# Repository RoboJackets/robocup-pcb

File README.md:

RoboCup PCB Repository
===========
Welcome to the Georgia Tech RoboJackets repository for management and storage of RoboCup's hardware files! Additional information about the team and current projects can be found on the [RoboJackets Website](http://www.robojackets.org/teams/robocup/) and the [RoboJacket Wiki](http://wiki.robojackets.org/w/RoboCup).

If you are a new member to the RoboCup electrical team and have never used *[git version control](http://git-scm.com/)* before, we highly recommend that you familiarize yourself with it by reading [this guide](https://git-scm.com/book/en/v2).

## Prerequisites
- A computer configured with git [[Linux (Preferred)](https://git-scm.com/install/linux)] [[Windows](https://windows.github.com)] [[Mac](https://mac.github.com/)]
- An installation of [KiCAD v10.0](http://kicad-pcb.org/download/)
- An installation of [Obsidian](https://obsidian.md/download)

## Setup

### Cloning the Repository
To clone the repository, run the following command in your terminal:
```
git clone git@github.com:RoboJackets/robocup-pcb.git
```

## Board Archives
All currently deployed boards as of 2026 were designed using KiCAD.

However, older boards in the archives were designed using [EAGLE](http://www.cadsoftusa.com/) or [PCB](http://pcb.geda-project.org) (a program that is part of the [gEDA project](http://www.geda-project.org))

Unfortunately, EAGLE and PCB are no longer supported by their respective companies, and are not available for download. If you need access to these files, you are on your own.

## License

This project is licensed under the Apache License v2.0.  See the [LICENSE](LICENSE) file for more information.

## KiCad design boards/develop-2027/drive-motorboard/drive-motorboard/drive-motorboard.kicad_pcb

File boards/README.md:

# Style Guide

## Schematic Style
* Always snap to 0.1 inch grid
* Insert appropriate size frame for each sheet
    * Set Global Attributes for `REVISION` and `TEAM`
    * Set Attribute of frame for `SCH_DESC`

## Board Style
* Attempt to keep snapped to 0.5 mm (with 0.25 alt) with 90º or 45º angles

## Library Style
#### Symbol
* Always keep pins aligned to 0.1 inch grid
* Add Name and Value on correct layers

#### Package
* Add Name and Value on correct layers
* Silkscreen on `TPLACE` should not go over pad
* Use `TDOCU` to show accurate package outline

#### Device
* Final Device ideally be actual part number unless generic part where many possibles could be used
* Use wildcard when using multiple packages with one symbol
* Add correct prefix for component type ([reference](https://en.wikipedia.org/wiki/Reference_designator)), common components:
    * C : Capacitor
    * L : Inductor
    * R : Resistor
    * D : Diodes (including LEDs)
    * J : Jack (least movable part of connector)
    * Q : Transistor
    * F : Fuse
* Add manufacturer part number and (when possible) Digikey part number as attributes `MPN` and `DIGIKEY` respectivly
    * Do this for each technology and variant combination

# Finalize Board

When board completely done and ready to order ensure the following are completed:
* Board folder named "board-name"-v"version"
* Export board to PNG and place in folder
* Create README.md with description of the board and PNG of the board
* Create gerber.zip file of all Gerber files to be sent to board fab
* After all items added for board, make final commit for board version and tag commit as "board-name"-v"version"
* Once pushed to Github create release of board from tag consisting of list of changes from past version, link to gerber.zip (Github raw link for that tag), and PNG of board
    * For prototypes mark release as pre-release

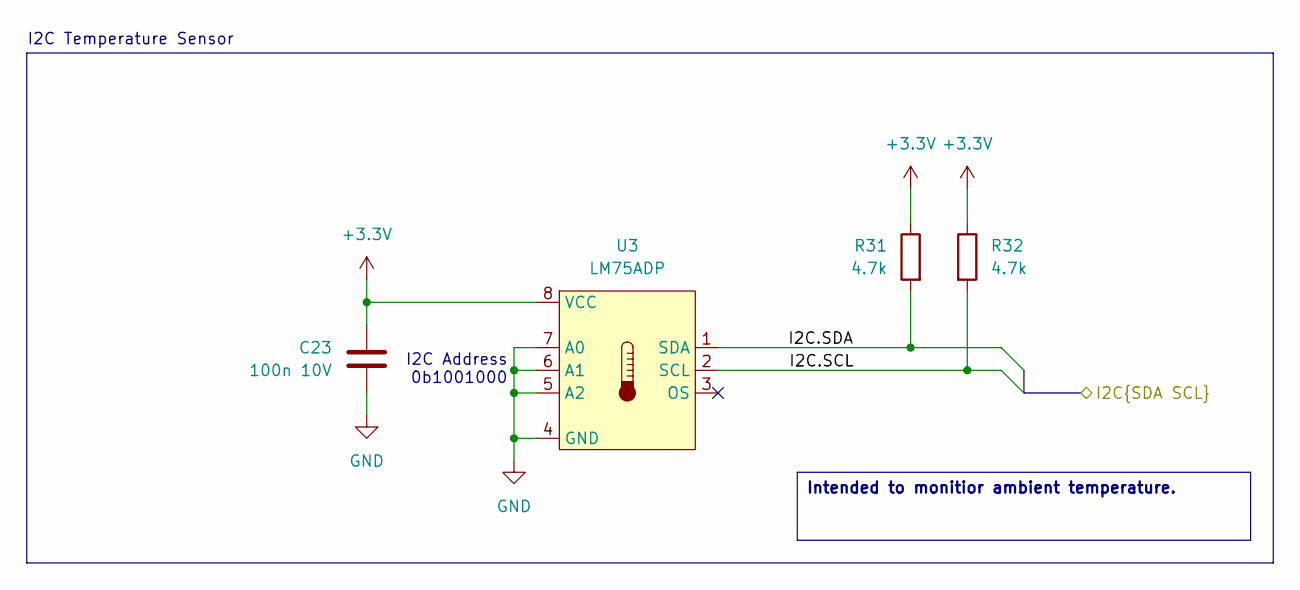
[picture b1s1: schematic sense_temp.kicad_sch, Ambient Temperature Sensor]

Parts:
C23: 100n 10V; C_0402_1005Metric; Manufacturer P/N CL05A104KA5NNNC
R31, R32: 4.7k; R_0402_1005Metric; Manufacturer P/N RC0402FR-074K7L
U3: LM75ADP; TSSOP-8_3x3mm_P0.65mm; Manufacturer P/N LM75ADP,118

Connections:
+3.3V: C23.1, R31.1, R32.1, U3.8 (VCC); also elsewhere on the board
/Motor Controller/I2C.SCL: R32.2, U3.2 (SCL); also elsewhere on the board
/Motor Controller/I2C.SDA: R31.2, U3.1 (SDA); also elsewhere on the board
GND: C23.2, U3.4 (GND), U3.5 (A2), U3.6 (A1), U3.7 (A0); also elsewhere on the board

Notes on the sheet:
I2C Address 0b1001000
I2C Temperature Sensor
Intended to monitior ambient temperature.

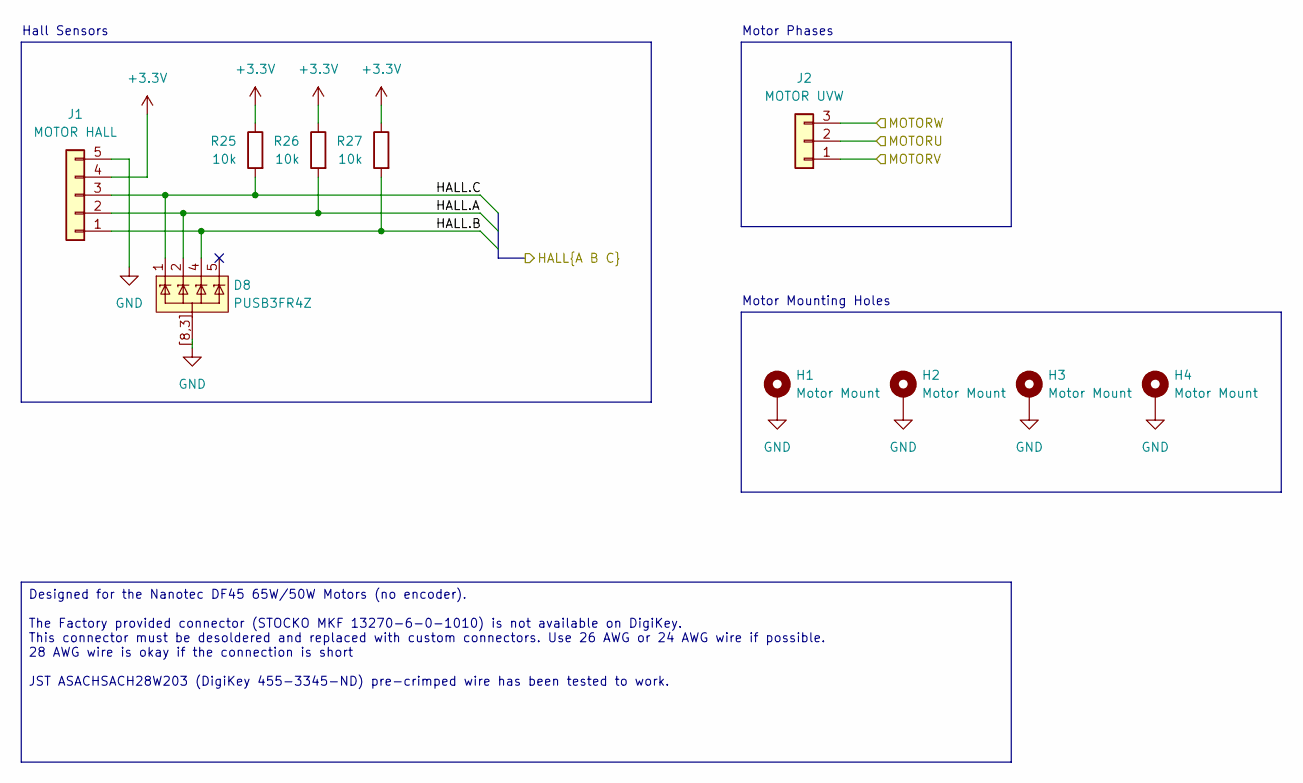
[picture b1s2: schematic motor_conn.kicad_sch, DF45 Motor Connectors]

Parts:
D8: PUSB3FR4Z; Diodes_UDFN-10_1x2.5mm_P0.5mm; Manufacturer P/N PUSB3FR4Z
H1: Motor Mount; MountingHole_3.2mm_M3_Pad; Manufacturer P/N H1
H2: Motor Mount; MountingHole_3.2mm_M3_Pad; Manufacturer P/N H2
H3: Motor Mount; MountingHole_3.2mm_M3_Pad; Manufacturer P/N H3
H4: Motor Mount; MountingHole_3.2mm_M3_Pad; Manufacturer P/N H4
J1: MOTOR HALL; JST_ACH_BM05B-ACHSS-A-GAN-ETF_1x05-1MP_P1.20mm_Vertical; Manufacturer P/N BM05B-ACHSS-A-GAN-ETF
J2: MOTOR UVW; JST_ACH_BM03B-ACHSS-GAN-ETF_1x03-1MP_P1.20mm_Vertical; Manufacturer P/N BM03B-ACHSS-GAN-TF
R25, R26, R27: 10k; R_0402_1005Metric; Manufacturer P/N RC0402FR-0710KL

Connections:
+3.3V: J1.4, R25.1, R26.1, R27.1; also elsewhere on the board
/Motor Connections/HALL.A: D8.2 (CH2), J1.2, R26.2; also elsewhere on the board
/Motor Connections/HALL.B: D8.4 (CH3), J1.1, R27.2; also elsewhere on the board
/Motor Connections/HALL.C: D8.1 (CH1), J1.3, R25.2; also elsewhere on the board
/Motor Connections/MOTORU: J2.2; also elsewhere on the board
/Motor Connections/MOTORV: J2.1; also elsewhere on the board
/Motor Connections/MOTORW: J2.3; also elsewhere on the board
GND: D8.3 (GND), D8.8 (GND), D8.[8,3] (GND), H1.1 (1_1), H2.1 (1_1), H3.1 (1_1), H4.1 (1_1), J1.5; also elsewhere on the board

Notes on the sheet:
Hall Sensors
Motor Phases
Motor Mounting Holes
Designed for the Nanotec DF45 65W/50W Motors (no encoder). The Factory provided connector (STOCKO MKF 13270-6-0-1010) is not available on DigiKey. This connector must be desoldered and replaced with custom connectors. Use 26 AWG or 24 AWG wire if possible. 28 AWG wire is okay if the connection is s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

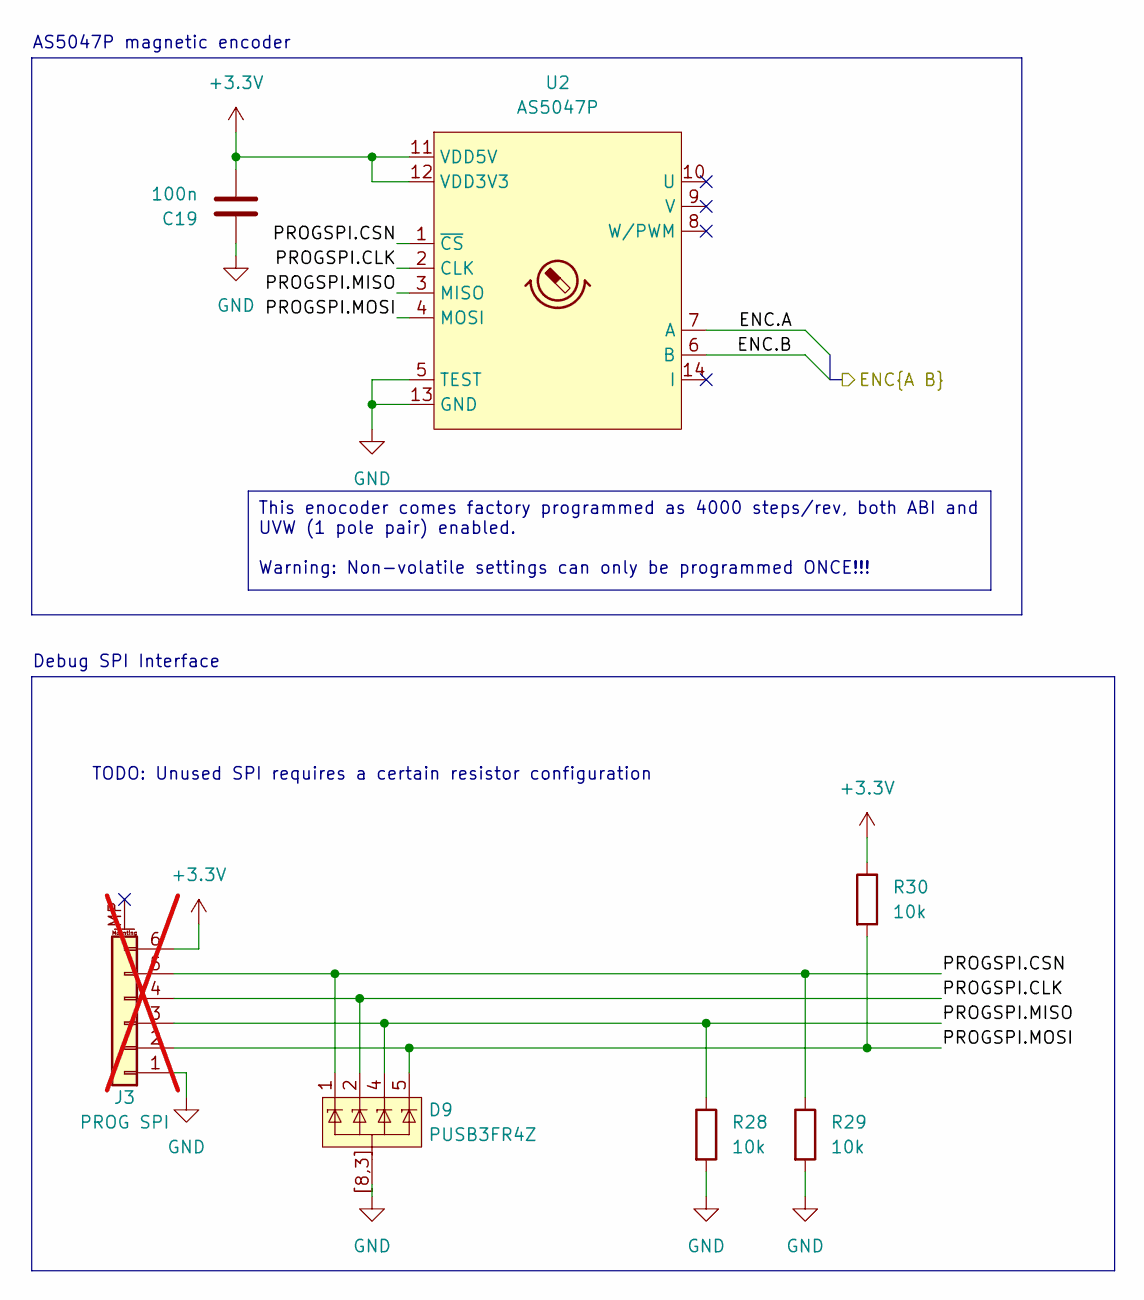
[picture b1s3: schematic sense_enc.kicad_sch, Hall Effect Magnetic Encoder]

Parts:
C19: 100n; C_0402_1005Metric; Manufacturer P/N CL05A104KA5NNNC
D9: PUSB3FR4Z; Diodes_UDFN-10_1x2.5mm_P0.5mm; Manufacturer P/N PUSB3FR4Z
J3: PROG SPI; JST_GH_SM06B-GHS-TB_1x06-1MP_P1.25mm_Horizontal; Manufacturer P/N SM06B-GHS-TB; not fitted
R28, R29, R30: 10k; R_0402_1005Metric; Manufacturer P/N RC0402FR-0710KL
U2: AS5047P; TSSOP-14_4.4x5mm_P0.65mm; Manufacturer P/N AS5047P

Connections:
+3.3V: C19.2, J3.6, R30.1, U2.11 (VDD5V), U2.12 (VDD3V3); also elsewhere on the board
/Magnetic Encoder/ENC.A: U2.7 (A); also elsewhere on the board
/Magnetic Encoder/ENC.B: U2.6 (B); also elsewhere on the board
/Magnetic Encoder/PROGSPI.CLK: D9.2 (CH2), J3.4, U2.2 (CLK)
/Magnetic Encoder/PROGSPI.CSN: D9.1 (CH1), J3.5, R29.1, U2.1 (~CS)
/Magnetic Encoder/PROGSPI.MISO: D9.4 (CH3), J3.3, R28.1, U2.3 (MISO)
/Magnetic Encoder/PROGSPI.MOSI: D9.5 (CH4), J3.2, R30.2, U2.4 (MOSI)
GND: C19.1, D9.3 (GND), D9.8 (GND), D9.[8,3] (GND), J3.1, R28.2, R29.2, U2.5 (TEST), U2.13 (GND); also elsewhere on the board

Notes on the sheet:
TODO: Unused SPI requires a certain resistor configuration
Debug SPI Interface
AS5047P magnetic encoder
This enocoder comes factory programmed as 4000 steps/rev, both ABI and UVW (1 pole pair) enabled. Warning: Non-volatile settings can only be programmed ONCE!!!

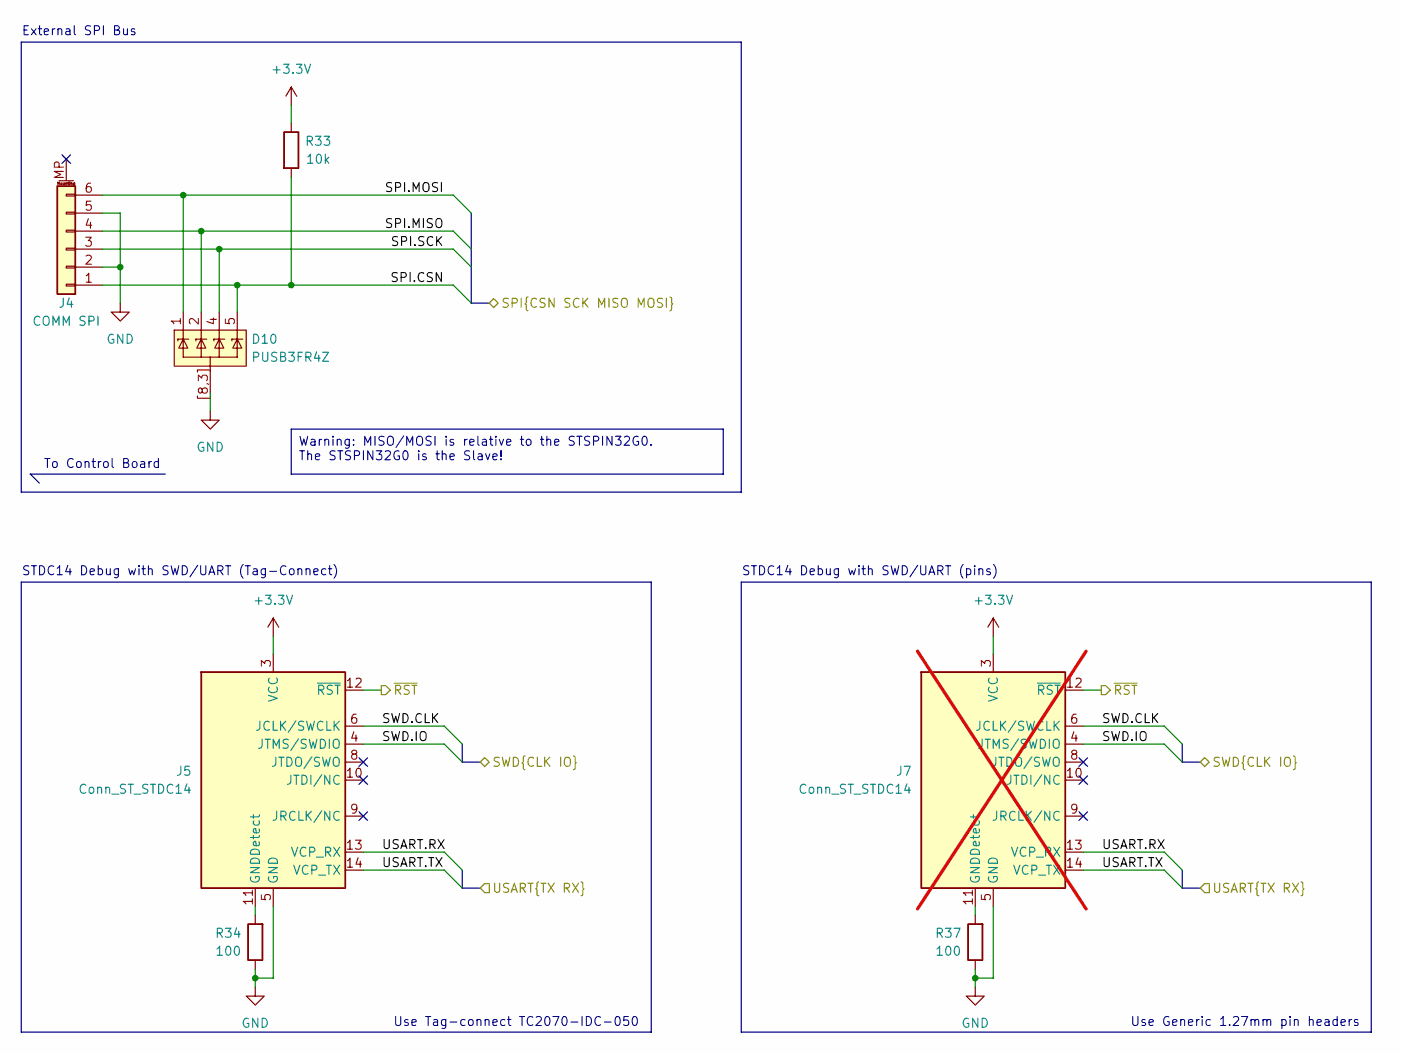
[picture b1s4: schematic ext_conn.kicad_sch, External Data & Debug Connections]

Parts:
D10: PUSB3FR4Z; Diodes_UDFN-10_1x2.5mm_P0.5mm; Manufacturer P/N PUSB3FR4Z
J4: COMM SPI; JST_GH_SM06B-GHS-TB_1x06-1MP_P1.25mm_Horizontal; Manufacturer P/N SM06B-GHS-TB
J5: Conn_ST_STDC14; Tag-Connect_TC2070-IDC-FP_2x07_P1.27mm_Vertical; Manufacturer P/N J5
J7: Conn_ST_STDC14; PinHeader_2x07_P1.27mm_Vertical_SMD; Manufacturer P/N FTSH-107-01-L-DV-K; not fitted
R33: 10k; R_0402_1005Metric; Manufacturer P/N RC0402FR-0710KL
R34, R37: 100; R_0402_1005Metric; Manufacturer P/N RC0402FR-07100RL

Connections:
+3.3V: J5.3 (VCC), J7.3 (VCC), R33.1; also elsewhere on the board
/External Connections/SPI.CSN: D10.5 (CH4), J4.1, R33.2; also elsewhere on the board
/External Connections/SPI.MISO: D10.2 (CH2), J4.4; also elsewhere on the board
/External Connections/SPI.MOSI: D10.1 (CH1), J4.6; also elsewhere on the board
/External Connections/SPI.SCK: D10.4 (CH3), J4.3; also elsewhere on the board
/External Connections/SWD.CLK: J5.6 (JCLK/SWCLK), J7.6 (JCLK/SWCLK); also elsewhere on the board
/External Connections/SWD.IO: J5.4 (JTMS/SWDIO), J7.4 (JTMS/SWDIO); also elsewhere on the board
/External Connections/USART.RX: J5.13 (VCP_RX), J7.13 (VCP_RX); also elsewhere on the board
/External Connections/USART.TX: J5.14 (VCP_TX), J7.14 (VCP_TX); also elsewhere on the board
/External Connections/~RST: J5.12 (~RST), J7.12 (~RST); also elsewhere on the board
GND: D10.3 (GND), D10.8 (GND), D10.[8,3] (GND), J4.2, J4.5, J5.5 (GND), J5.7 (GND), J7.5 (GND), J7.7 (GND), R34.1, R37.1; also elsewhere on the board
unnamed: J5.11 (GNDDetect), R34.2
unnamed: J7.11 (GNDDetect), R37.2

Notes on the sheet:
External SPI Bus
To Control Board
STDC14 Debug with SWD/UART (pins)
STDC14 Debug with SWD/UART (Tag-Connect)
Use Generic 1.27mm pin headers
Use Tag-connect TC2070-IDC-050
Warning: MISO/MOSI is relative to the STSPIN32G0. The STSPIN32G0 is the Slave!

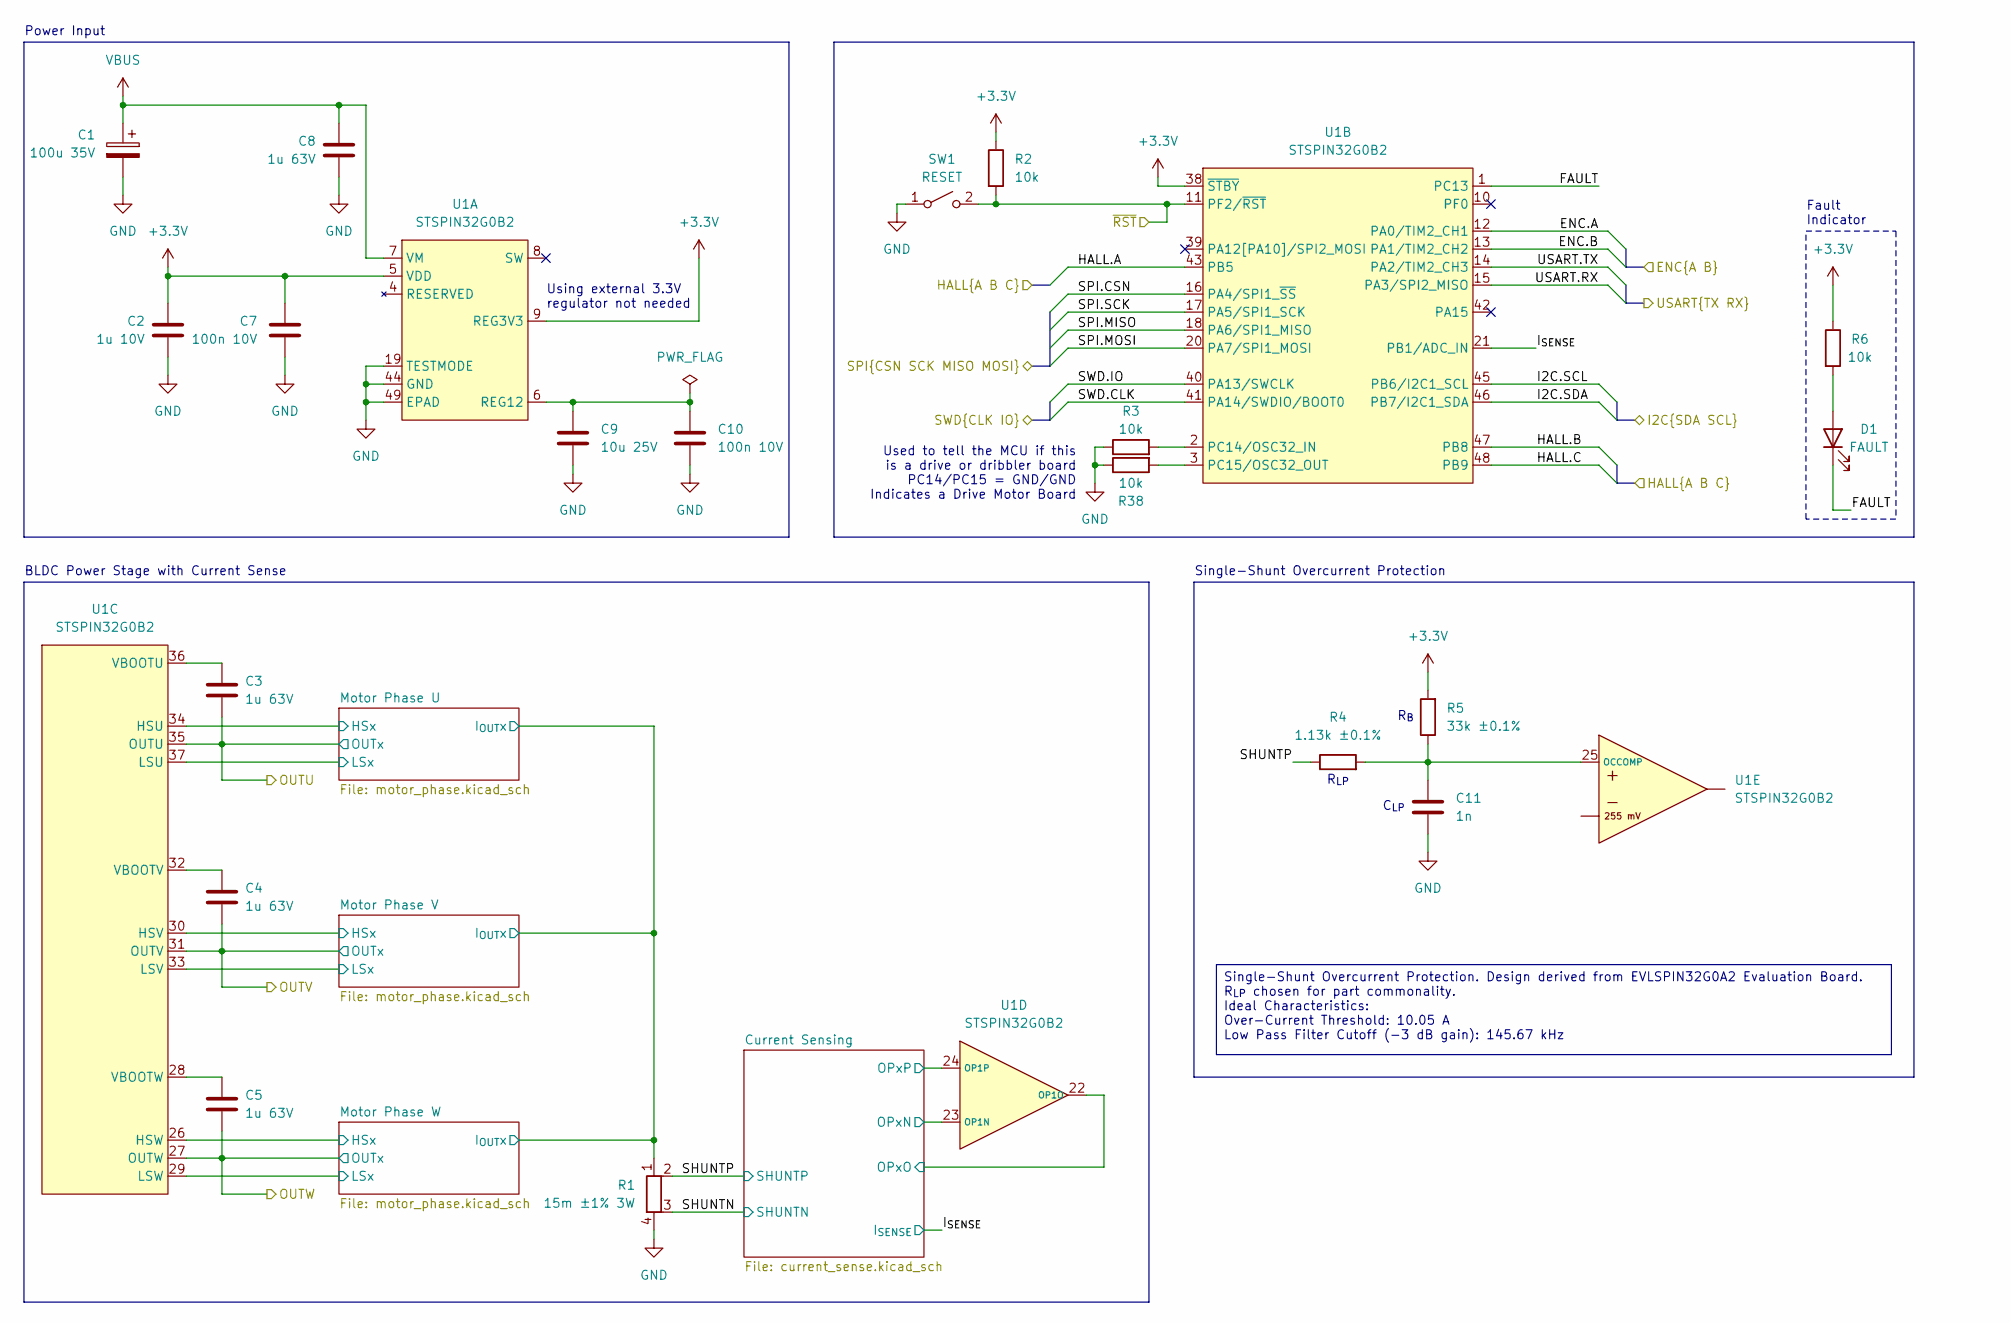
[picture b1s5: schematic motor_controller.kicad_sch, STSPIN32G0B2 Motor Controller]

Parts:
C1: 100u 35V; C_Elec_6.3x5.8; Manufacturer P/N EEE-FT1V101AP
C2: 1u 10V; C_0603_1608Metric; Manufacturer P/N CL10B105KB8NQNC
C3, C4, C5, C8: 1u 63V; C_0603_1608Metric; Manufacturer P/N CL10B105KB8NQNC
C7, C10: 100n 10V; C_0402_1005Metric; Manufacturer P/N CL05A104KA5NNNC
C9: 10u 25V; C_0603_1608Metric; Manufacturer P/N GRM188R6YA106MA73D
C11: 1n; C_0402_1005Metric; Manufacturer P/N CL05B102KB5NNNC
D1: FAULT; LED_0603_1608Metric; Manufacturer P/N LTST-C190KRKT
R1: 15m ±1% 3W; R_Shunt_Analog_2512_6332_HighAccuracy; Manufacturer P/N CRA2512-FZ-R015ELF
R2, R3, R6, R38: 10k; R_0402_1005Metric; Manufacturer P/N RC0402FR-0710KL
R4: 1.13k ±0.1%; R_0402_1005Metric; Manufacturer P/N RT0402BRD071K13L
R5: 33k ±0.1%; R_0402_1005Metric; Manufacturer P/N AT0402BRD0733KL
SW1: RESET; SW_Push_1P1T_NO_CK_KMR2; Manufacturer P/N KMR221NGLFS
U1: STSPIN32G0B2; VQFN-48-1EP_7x7mm_P0.5mm_EP2.6x2.6mm; Manufacturer P/N STSPIN32G0B2

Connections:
+3.3V: C2.1, C7.1, R2.1, R5.2, R6.1, U1.5 (VDD), U1.9 (REG3V3), U1.38 (~STBY); also elsewhere on the board
/External Connections/SPI.CSN: U1.16 (PA4/SPI1_~SS); also elsewhere on the board
/External Connections/SPI.MISO: U1.18 (PA6/SPI1_MISO); also elsewhere on the board
/External Connections/SPI.MOSI: U1.20 (PA7/SPI1_MOSI); also elsewhere on the board
/External Connections/SPI.SCK: U1.17 (PA5/SPI1_SCK); also elsewhere on the board
/External Connections/SWD.CLK: U1.41 (PA14/SWDIO/BOOT0); also elsewhere on the board
/External Connections/SWD.IO: U1.40 (PA13/SWCLK); also elsewhere on the board
/External Connections/USART.RX: U1.15 (PA3/SPI2_MISO); also elsewhere on the board
/External Connections/USART.TX: U1.14 (PA2/TIM2_CH3); also elsewhere on the board
/External Connections/~RST: R2.2, SW1.2 (B), U1.11 (PF2/~RST); also elsewhere on the board
/Magnetic Encoder/ENC.A: U1.12 (PA0/TIM2_CH1); also elsewhere on the board
/Magnetic Encoder/ENC.B: U1.13 (PA1/TIM2_CH2); also elsewhere on the board
/Motor Connections/HALL.A: U1.43 (PB5); also elsewhere on the board
/Motor Connections/HALL.B: U1.47 (PB8); also elsewhere on the board
/Motor Connections/HALL.C: U1.48 (PB9); also elsewhere on the board
/Motor Connections/MOTORU: C3.2, U1.35 (OUTU); also elsewhere on the board
/Motor Connections/MOTORV: C4.2, U1.31 (OUTV); also elsewhere on the board
/Motor Connections/MOTORW: C5.2, U1.27 (OUTW); also elsewhere on the board
/Motor Controller/Current Sensing/OPxN: U1.23 (OP1N); also elsewhere on the board
/Motor Controller/Current Sensing/OPxO: U1.22 (OP1O); also elsewhere on the board
/Motor Controller/Current Sensing/OPxP: U1.24 (OP1P); also elsewhere on the board
/Motor Controller/FAULT: D1.1 (K), U1.1 (PC13)
/Motor Controller/I2C.SCL: U1.45 (PB6/I2C1_SCL); also elsewhere on the board
/Motor Controller/I2C.SDA: U1.46 (PB7/I2C1_SDA); also elsewhere on the board
/Motor Controller/I_{SENSE}: U1.21 (PB1/ADC_IN); also elsewhere on the board
/Motor Controller/Motor Phase U/HSx: U1.34 (HSU); also elsewhere on the board
/Motor Controller/Motor Phase U/I_{OUT}x: R1.1; also elsewhere on the board
/Motor Controller/Motor Phase U/LSx: U1.37 (LSU); also elsewhere on the board
/Motor Controller/Motor Phase V/HSx: U1.30 (HSV); also elsewhere on the board
/Motor Controller/Motor Phase V/LSx: U1.33 (LSV); also elsewhere on the board
/Motor Controller/Motor Phase W/HSx: U1.26 (HSW); also elsewhere on the board
/Motor Controller/Motor Phase W/LSx: U1.29 (LSW); also elsewhere on the board
/Motor Controller/SHUNTN: R1.3; also elsewhere on the board
/Motor Controller/SHUNTP: R1.2, R4.1; also elsewhere on the board
GND: C1.2, C2.2, C7.2, C8.2, C9.2, C10.2, C11.2, R1.4, R3.1, R38.1, SW1.1 (A), U1.19 (TESTMODE), U1.44 (GND), U1.49 (EPAD); also elsewhere on the board
unnamed: D1.2 (A), R6.2
unnamed: C3.1, U1.36 (VBOOTU)
unnamed: C4.1, U1.32 (VBOOTV)
unnamed: C5.1, U1.28 (VBOOTW)
unnamed: R3.2, U1.2 (PC14/OSC32_IN)
unnamed: R38.2, U1.3 (PC15/OSC32_OUT)
unnamed: C11.1, R4.2, R5.1, U1.25 (OCCOMP)
unnamed: C9.1, C10.1, U1.6 (REG12)
VBUS: C1.1, C8.1, U1.7 (VM); also elsewhere on the board

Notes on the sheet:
BLDC Power Stage with Current Sense
Fault Indicator
Power Input
R_{LP}
Single-Shunt Overcurrent Protection
C_{LP}
Used to tell the MCU if this is a drive or dribbler board PC14/PC15 = GND/GND Indicates a Drive Motor Board
R_{B}
Using external 3.3V regulator not needed
Single-Shunt Overcurrent Protection. Design derived from EVLSPIN32G0A2 Evaluation Board. R_{LP} chosen for part commonality. Ideal Characteristics: Over-Current Threshold: 10.05 A Low Pass Filter Cutoff (-3 dB gain): 145.67 kHz

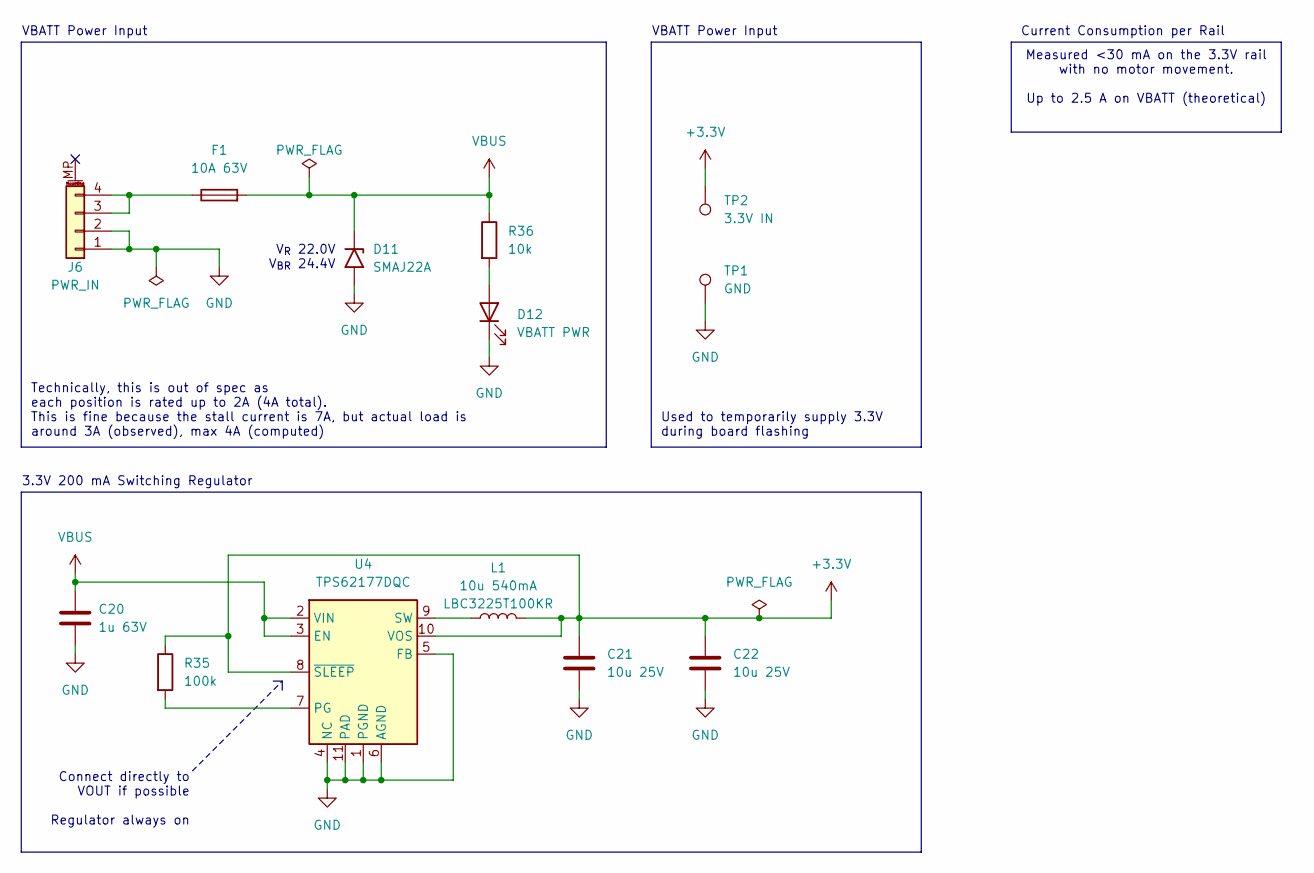
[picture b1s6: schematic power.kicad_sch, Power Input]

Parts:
C20: 1u 63V; C_0603_1608Metric; Manufacturer P/N CL10B105KB8NQNC
C21, C22: 10u 25V; C_0603_1608Metric; Manufacturer P/N GRM188R6YA106MA73D
D11: SMAJ22A; D_SMA; Manufacturer P/N C134971
D12: VBATT PWR; LED_0603_1608Metric; Manufacturer P/N LTST-C190KGKT
F1: 10A 63V; Fuse_1206_3216Metric_Pad1.42x1.75mm_HandSolder; Manufacturer P/N 3413.0328.22
J6: PWR_IN; JST_PH_S4B-PH-SM4-TB_1x04-1MP_P2.00mm_Horizontal; Manufacturer P/N S4B-PH-SM4-TB
L1: 10u 540mA; L_1210_3225Metric; Manufacturer P/N LBC3225T100KR
R35: 100k; R_0402_1005Metric; Manufacturer P/N RC0402FR-07100KL
R36: 10k; R_0402_1005Metric; Manufacturer P/N RC0402FR-0710KL
TP1: GND; TestPoint_Pad_3.0x3.0mm
TP2: 3.3V IN; TestPoint_Pad_3.0x3.0mm
U4: TPS62177DQC; WSON-10-1EP_2x3mm_P0.5mm_EP0.84x2.4mm; Manufacturer P/N TPS62177DQC

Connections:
+3.3V: C21.1, C22.1, L1.2, R35.1, TP2.1 (1_1), U4.8 (~SLEEP), U4.10 (VOS); also elsewhere on the board
GND: C20.2, C21.2, C22.2, D11.2 (A2), D12.1 (K), J6.1, J6.2, TP1.1 (1_1), U4.1 (PGND), U4.4 (NC), U4.5 (FB), U4.6 (AGND), U4.11 (PAD); also elsewhere on the board
unnamed: D12.2 (A), R36.2
unnamed: F1.1, J6.3, J6.4
unnamed: R35.2, U4.7 (PG)
unnamed: L1.1, U4.9 (SW)
VBUS: C20.1, D11.1 (A1), F1.2, R36.1, U4.2 (VIN), U4.3 (EN); also elsewhere on the board

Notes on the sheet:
Used to temporarily supply 3.3V during board flashing
3.3V 200 mA Switching Regulator
VBATT Power Input
Measured <30 mA on the 3.3V rail with no motor movement. Up to 2.5 A on VBATT (theoretical)
V_{R} 22.0V V_{BR} 24.4V
Technically, this is out of spec as each position is rated up to 2A (4A total). This is fine because the stall current is 7A, but actual load is around 3A (observed), max 4A (computed)
Current Consumption per Rail
Connect directly to VOUT if possible Regulator always on

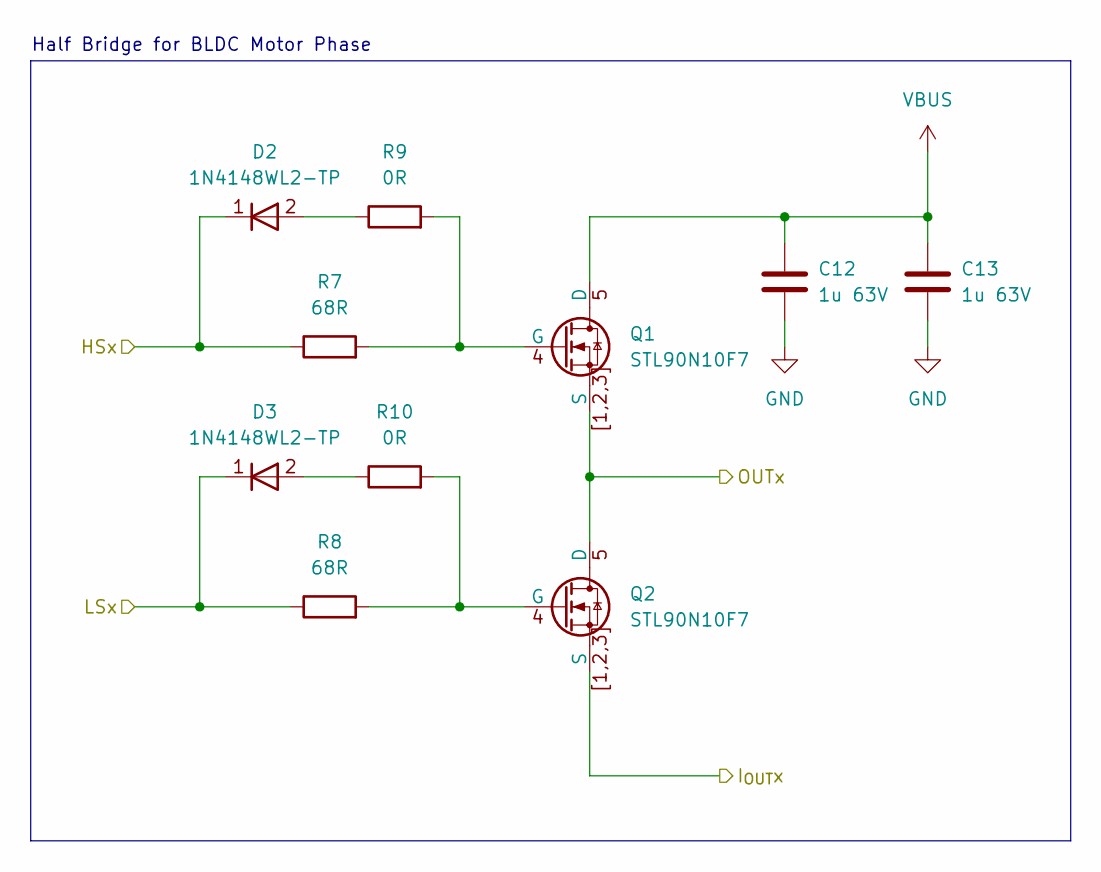
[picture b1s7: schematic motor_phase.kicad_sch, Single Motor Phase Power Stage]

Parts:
C12, C13: 1u 63V; C_0603_1608Metric; Manufacturer P/N CL10B105KB8NQNC
D2, D3: 1N4148WL2-TP; D_SOD-882; Manufacturer P/N 1N4148WL2-TP
Q1, Q2: STL90N10F7; PQFN-8-EP_6x5mm_P1.27mm_Generic; Manufacturer P/N STL90N10F7
R7, R8: 68R; R_0402_1005Metric; Manufacturer P/N RC0402FR-0768RL
R9, R10: 0R; R_0402_1005Metric; Manufacturer P/N RC0402JR-070RL

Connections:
/Motor Connections/MOTORU: Q1.1 (S), Q1.2 (S), Q1.3 (S), Q1.[1,2,3] (S), Q2.5 (D); also elsewhere on the board
/Motor Controller/Motor Phase U/HSx: D2.1 (K), R7.1; also elsewhere on the board
/Motor Controller/Motor Phase U/I_{OUT}x: Q2.1 (S), Q2.2 (S), Q2.3 (S); also elsewhere on the board
/Motor Controller/Motor Phase U/LSx: D3.1 (K), R8.1; also elsewhere on the board
GND: C12.2, C13.2; also elsewhere on the board
unnamed: D2.2 (A), R9.1
unnamed: D3.2 (A), R10.1
unnamed: Q1.4 (G), R7.2, R9.2
unnamed: Q2.4 (G), R8.2, R10.2
VBUS: C12.1, C13.1, Q1.5 (D); also elsewhere on the board

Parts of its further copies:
C14, C15, C16, C17: 1u 63V; C_0603_1608Metric; Manufacturer P/N CL10B105KB8NQNC
D4, D5, D6, D7: 1N4148WL2-TP; D_SOD-882; Manufacturer P/N 1N4148WL2-TP
Q3, Q4, Q5, Q6: STL90N10F7; PQFN-8-EP_6x5mm_P1.27mm_Generic; Manufacturer P/N STL90N10F7
R11, R12, R15, R16: 68R; R_0402_1005Metric; Manufacturer P/N RC0402FR-0768RL
R13, R14, R17, R18: 0R; R_0402_1005Metric; Manufacturer P/N RC0402JR-070RL

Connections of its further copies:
/Motor Connections/MOTORV: Q3.1 (S), Q3.2 (S), Q3.3 (S), Q4.5 (D); also elsewhere on the board
/Motor Connections/MOTORW: Q5.1 (S), Q5.2 (S), Q5.3 (S), Q6.5 (D); also elsewhere on the board
/Motor Controller/Motor Phase U/I_{OUT}x: Q4.1 (S), Q4.2 (S), Q4.3 (S), Q6.1 (S), Q6.2 (S), Q6.3 (S); also elsewhere on the board
/Motor Controller/Motor Phase V/HSx: D4.1 (K), R11.1; also elsewhere on the board
/Motor Controller/Motor Phase V/LSx: D5.1 (K), R12.1; also elsewhere on the board
/Motor Controller/Motor Phase W/HSx: D6.1 (K), R15.1; also elsewhere on the board
/Motor Controller/Motor Phase W/LSx: D7.1 (K), R16.1; also elsewhere on the board
GND: C14.2, C15.2, C16.2, C17.2; also elsewhere on the board
unnamed: D4.2 (A), R13.1
unnamed: D5.2 (A), R14.1
unnamed: D6.2 (A), R17.1
unnamed: D7.2 (A), R18.1
unnamed: Q3.4 (G), R11.2, R13.2
unnamed: Q4.4 (G), R12.2, R14.2
unnamed: Q5.4 (G), R15.2, R17.2
unnamed: Q6.4 (G), R16.2, R18.2
VBUS: C14.1, C15.1, C16.1, C17.1, Q3.5 (D), Q5.5 (D); also elsewhere on the board

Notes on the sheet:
Half Bridge for BLDC Motor Phase

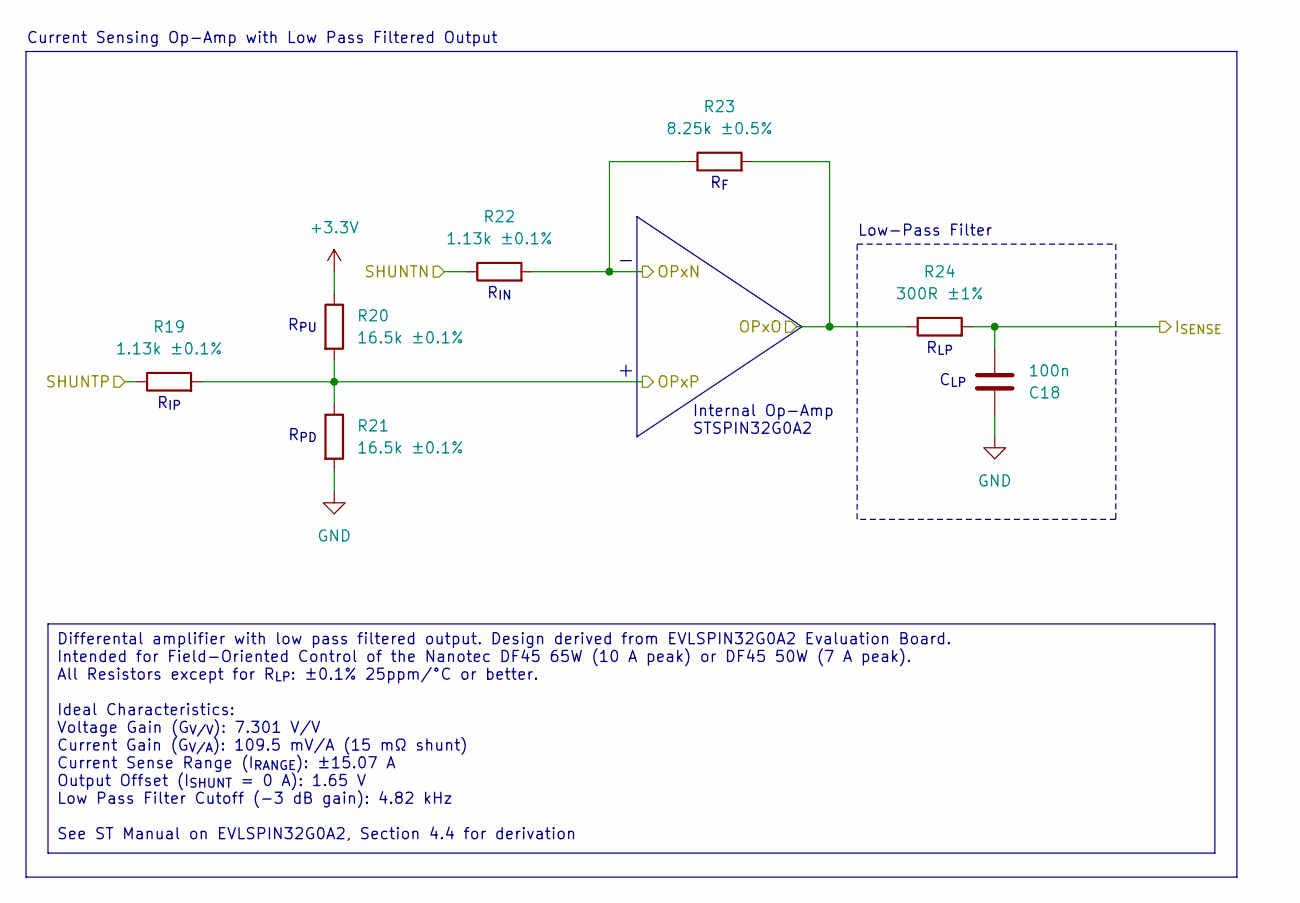
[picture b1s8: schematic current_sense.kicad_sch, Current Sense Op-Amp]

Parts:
C18: 100n; C_0402_1005Metric; Manufacturer P/N CL05A104KA5NNNC
R19, R22: 1.13k ±0.1%; R_0402_1005Metric; Manufacturer P/N RT0402BRD071K13L
R20, R21: 16.5k ±0.1%; R_0402_1005Metric; Manufacturer P/N RT0402BRD0716K5L
R23: 8.25k ±0.5%; R_0201_0603Metric; Manufacturer P/N RC0201DR-078K25L
R24: 300R ±1%; R_0201_0603Metric; Manufacturer P/N RC0201FR-07300RL

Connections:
+3.3V: R20.1; also elsewhere on the board
/Motor Controller/Current Sensing/OPxN: R22.2, R23.1; also elsewhere on the board
/Motor Controller/Current Sensing/OPxO: R23.2, R24.1; also elsewhere on the board
/Motor Controller/Current Sensing/OPxP: R19.2, R20.2, R21.1; also elsewhere on the board
/Motor Controller/I_{SENSE}: C18.2, R24.2; also elsewhere on the board
/Motor Controller/SHUNTN: R22.1; also elsewhere on the board
/Motor Controller/SHUNTP: R19.1; also elsewhere on the board
GND: C18.1, R21.2; also elsewhere on the board

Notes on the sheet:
R_{PU}
C_{LP}
Low-Pass Filter
R_{F}
R_{PD}
R_{IP}
Current Sensing Op-Amp with Low Pass Filtered Output
Internal Op-Amp STSPIN32G0A2
R_{LP}
R_{IN}
Differental amplifier with low pass filtered output. Design derived from EVLSPIN32G0A2 Evaluation Board. Intended for Field-Oriented Control of the Nanotec DF45 65W (10 A peak) or DF45 50W (7 A peak). All Resistors except for R_{LP}: ±0.1% 25ppm/°C or better. Ideal Characteristics: Voltage Gain (G_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

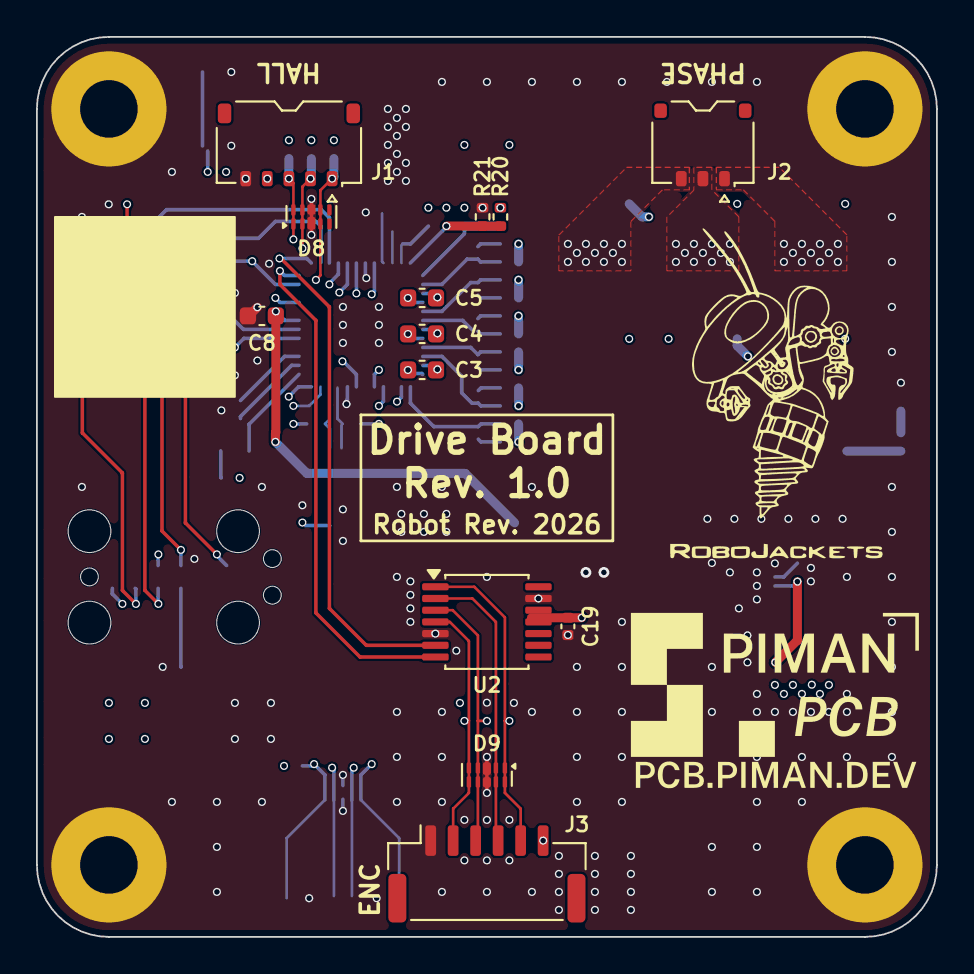
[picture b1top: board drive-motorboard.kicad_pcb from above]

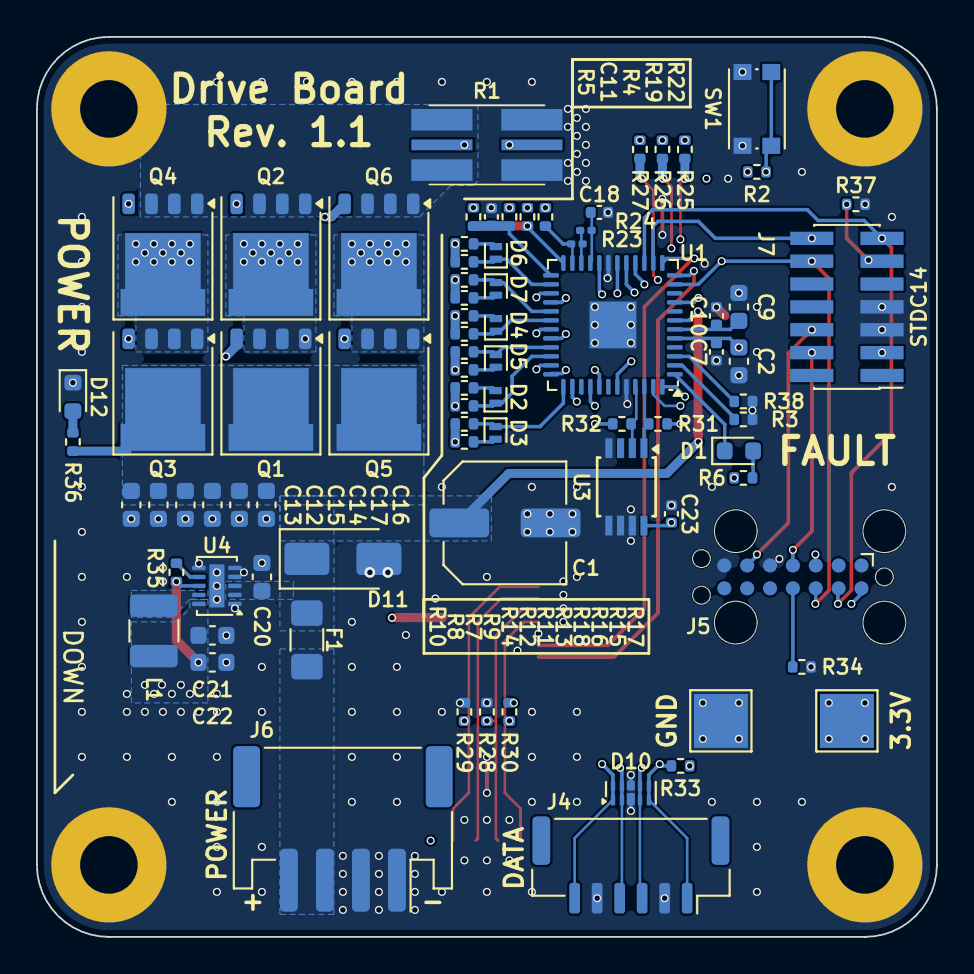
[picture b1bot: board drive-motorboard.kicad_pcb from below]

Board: 6 copper layers, 50.0 x 50.0 mm, 98 parts (81 on the bottom side), 66 nets.
